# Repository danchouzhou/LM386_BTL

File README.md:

# The Ultimate LM386 BTL Amplifier

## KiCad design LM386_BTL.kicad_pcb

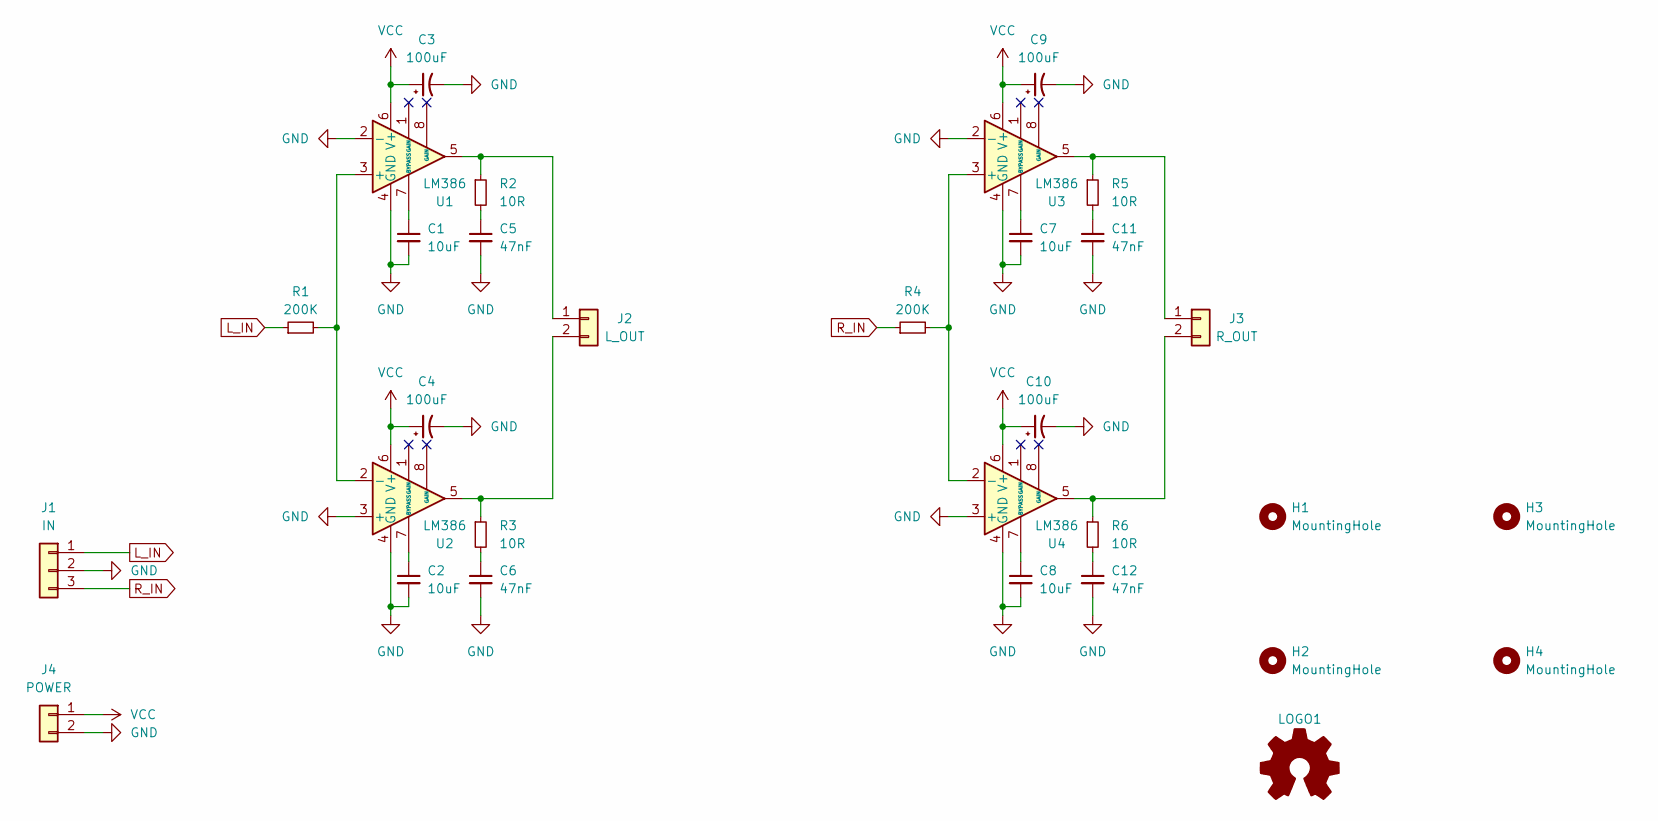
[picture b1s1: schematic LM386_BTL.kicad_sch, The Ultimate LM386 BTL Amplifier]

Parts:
C1, C2, C7, C8: 10uF; CP_Radial_D5.0mm_P2.00mm
C3, C4, C9, C10: 100uF; CP_Radial_D5.0mm_P2.00mm
C5, C6, C11, C12: 47nF; C_Disc_D5.0mm_W2.5mm_P5.00mm
H1, H2, H3, H4: MountingHole; MountingHole_3.2mm_M3_DIN965
J1: IN; JST_PH_B3B-PH-K_1x03_P2.00mm_Vertical
J2: L_OUT; JST_PH_B2B-PH-K_1x02_P2.00mm_Vertical
J3: R_OUT; JST_PH_B2B-PH-K_1x02_P2.00mm_Vertical
J4: POWER; JST_PH_B2B-PH-K_1x02_P2.00mm_Vertical
LOGO1: Logo_Open_Hardware_Small; OSHW-Logo_5.7x6mm_Copper
R1, R4: 200K; R_Axial_DIN0207_L6.3mm_D2.5mm_P10.16mm_Horizontal
R2, R3, R5, R6: 10R; R_Axial_DIN0207_L6.3mm_D2.5mm_P10.16mm_Horizontal
U1, U2, U3, U4: LM386; DIP-8_W7.62mm_Socket_LongPads

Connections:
GND: C1.2, C2.2, C3.2, C4.2, C5.2, C6.2, C7.2, C8.2, C9.2, C10.2, C11.2, C12.2, J1.2, J4.2, U1.2 (-), U1.4 (GND), U2.3 (+), U2.4 (GND), U3.2 (-), U3.4 (GND), U4.3 (+), U4.4 (GND)
L_IN: J1.1, R1.1
unnamed: C1.1, U1.7 (BYPASS)
unnamed: C2.1, U2.7 (BYPASS)
unnamed: C5.1, R2.2
unnamed: C6.1, R3.2
unnamed: C7.1, U3.7 (BYPASS)
unnamed: C8.1, U4.7 (BYPASS)
unnamed: C11.1, R5.2
unnamed: C12.1, R6.2
unnamed: J2.1, R2.1, U1.5
unnamed: J2.2, R3.1, U2.5
unnamed: J3.1, R5.1, U3.5
unnamed: J3.2, R6.1, U4.5
unnamed: R1.2, U1.3 (+), U2.2 (-)
unnamed: R4.2, U3.3 (+), U4.2 (-)
R_IN: J1.3, R4.1
VCC: C3.1, C4.1, C9.1, C10.1, J4.1, U1.6 (V+), U2.6 (V+), U3.6 (V+), U4.6 (V+)

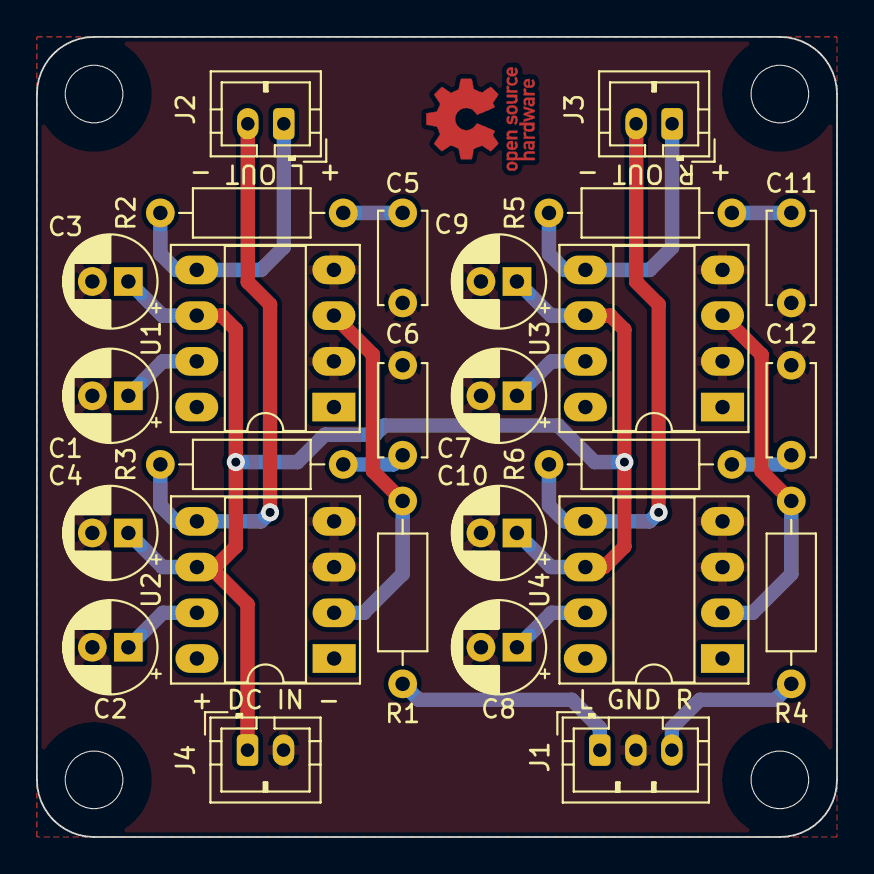
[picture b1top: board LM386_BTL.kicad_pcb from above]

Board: 2 copper layers, 44.5 x 44.5 mm, 31 parts (0 on the bottom side), 18 nets.

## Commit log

2022-12-21 Swap positive and negative amplifier position prevent from oscillation
2023-02-07 Swap output polarity
2023-03-18 Add photo
2023-10-06 Change capacitor footprint P2.50mm into P2.00mm

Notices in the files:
LM386_BTL.kicad_sch:
Copyright © Danny Chou, all rights reserved.
